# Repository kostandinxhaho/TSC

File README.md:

# OpenBook eReader

This project is a minimalist eBook Reader called **OpenBook**, built around the ESP32-C6 platform. The device is contains:

  - **A 7.5-inch e-paper display**

  - **A Li-Po battery**

  - **USB-C charging**

  - **Navigation buttons**

The design focuses on energy efficiency and ease of use, featuring a simple interface managed via GPIOs. The primary goal is to provide an optimal e-reading experience with low power consumption and a comfortable display.

## System Overview

| **Component** | **Details** |
|---------------|-------------|
| **MCU** | ESP32-C6 – supports Wi-Fi 6, BLE, Zigbee, and Thread |
| **Display** | 7.5-inch E-Paper (800 x 480 resolution, ~44g) |
| **Sensors** | BME688 – measures gas, humidity, temperature, and pressure |
| **Storage** | External NOR Flash 64MB (SPI) <br> SD Card (SPI) for extra storage |
| **Power Supply** | Battery: CELLEVIA BATTERIES LP584174 (3.7V, 1800mAh) <br> LDO Voltage Regulator for a steady 3.3V |
| **RTC** | Real-Time Clock for keeping time even when powered off |
| **Charging** | MCP73831T – charges via USB-C |
| **Extras** | Test Pads for debugging <br> Qwiic interface for easy module expansion |

## Block Diagram

## Bill of Materials:
| **Component** | **Purchase Link** | **Datasheet Link** |
|---------------|-------------------|---------------------|
| 112A-TAAR-R03 ATTEND | [Buy on Digi-Key](https://www.digikey.com/en/products/detail/attend-technology/112A-TAAR-R03/17633923) | [Datasheet](https://www.snapeda.com/parts/112A-TAAR-R03/Attend/datasheet/) |
| BDS229G-TR | [Buy on Digi-Key](https://www.digikey.com/en/products/detail/rohm-semiconductor/BDS229G-TR/3663792) | [Datasheet](https://fscdn.rohm.com/en/products/databook/datasheet/ic/power/voltage_detector/bds229g-e.pdf) |
| ESP32 WROVER BME680 Sensor | [Buy on Mouser](https://www.mouser.com/ProductDetail/Bosch-Sensortec/BME680) | [Datasheet](https://www.bosch-sensortec.com/media/boschsensortec/downloads/datasheets/bst-bme680-ds001.pdf) |
| LED CHG_LED | [Buy on Mouser](https://www.mouser.com/ProductDetail/Wurth-Elektronik/150060SS75000) | [Datasheet](https://www.we-online.com/components/products/datasheet/150060SS75000.pdf) |
| Condensator C0402 | [Buy on Digi-Key](https://www.digikey.com/en/products/detail/murata-electronics/GRM155R71C104KA88D/675947) | [Datasheet](https://search.murata.co.jp/Ceramy/image/img/A01X/G101/ENG/GRM155R71C104KA88-01.pdf) |
| Condensator Tant | [Buy on Digi-Key](https://www.digikey.com/en/products/detail/kemet/T491A106K016AT/2336183) | [Datasheet](https://search.kemet.com/download/datasheet/T491A106K016AT) |
| Q1 DMG2305UX-7 | [Buy on Mouser](https://www.mouser.com/ProductDetail/Diodes-Incorporated/DMG2305UX-7) | [Datasheet](https://www.diodes.com/assets/Datasheets/DMG2305UX.pdf) |
| RTC MODULE DS3231SN# | [Buy on Digi-Key](https://www.digikey.com/en/products/detail/analog-devices-inc-maxim-integrated/DS3231SN/1197576) | [Datasheet](https://www.analog.com/media/en/technical-documentation/data-sheets/DS3231.pdf) |
| ESP32 C6 WROOM-1-N8 | [Buy on Digi-Key](https://www.digikey.com/en/products/detail/espressif-systems/ESP32-C6-WROOM-1-N8/17728866) | [Datasheet](https://www.espressif.com/sites/default/files/documentation/esp32-c6-wroom-1_wroom-1u_datasheet_en.pdf) |
| FH34SRJ-24S-0.5SH(99) | [Buy on Digi-Key](https://www.digikey.com/en/products/detail/hirose-electric-co-ltd/FH34SRJ-24S-0-5SH-99/5132529) | [Datasheet](https://www.hirose.com/product/p/CL0580-1255-6-99) |
| MAX17048G+T10 | [Buy on Mouser](https://www.mouser.com/ProductDetail/Analog-Devices/MAX17048G+T10) | [Datasheet](https://www.analog.com/media/en/technical-documentation/data-sheets/max17048-max17049.pdf) |
| MBR0530 Schottky Diode | [Buy on Mouser](https://www.mouser.com/ProductDetail/onsemi/MBR0530T1G) | [Datasheet](https://www.onsemi.com/pdf/datasheet/mbr0530t1-d.pdf) |
| ESP32 WROVER MCP73831 Power Management | [Buy on Adafruit](https://www.adafruit.com/product/4410) | [Datasheet](https://ww1.microchip.com/downloads/en/DeviceDoc/20001984g.pdf) |
| PFMF.050.1 | [Buy on Mouser](https://www.mouser.com/ProductDetail/Littelfuse/PFMF050-1) | [Datasheet](https://www.littelfuse.com/~/media/electrical/datasheets/resettable-ptcs/littelfuse_ptc_pfmf_datasheet.pdf) |
| PGB1010603MR | [Buy on Mouser](https://www.mouser.com/ProductDetail/Littelfuse/PGB1010603MR) | [Datasheet](https://www.littelfuse.com/~/media/electrical/datasheets/esd_suppressors/littelfuse_esd_supressor_pulse_guard_pgb0603.pdf) |
| QWIIC_RIGHT_ANGLE CONNECTOR | [Buy on SparkFun](https://www.sparkfun.com/products/14427) | [Datasheet](https://www.jst-mfg.com/product/pdf/eng/eSR.pdf) |
| Rezistență R0402 | [Buy on Mouser](https://www.mouser.com/c/passive-components/resistors/?manu=Yageo%20Phycomp%7CYAGEO&resistance=10%20kOhms&package=%2Fcase%7C0402) | [Datasheet](https://www.yageo.com/upload/media/product/product_search/datasheet/cpr/yageo-rc_series_datasheet_2018.pdf) |
| SD0805S020S1R0 | [Buy on Digi-Key](https://www.digikey.com/en/products/detail/littelfuse-inc/SD0805S020S1R0/736561) | [Datasheet](https://www.littelfuse.com/~/media/electrical/datasheets/resettable-ptcs/littelfuse_ptc_sd0805_series.pdf) |
| Si1308EDL-T1-GE3 MOSFET | [Buy on Mouser](https://www.mouser.com/ProductDetail/Vishay/SI1308EDL-T1-GE3) | [Datasheet](https://www.vishay.com/docs/63442/si1308edl.pdf) |
| USB4110-GF-A | [Buy on Mouser](https://www.mouser.com/ProductDetail/GCT/USB4110-GF-A) | [Datasheet](https://gct.co/drawings/usb4110.pdf) |
| USBLC6-2SC6Y | [Buy on Mouser](https://www.mouser.com/ProductDetail/STMicroelectronics/USBLC6-2SC6Y) | [Datasheet](https://www.st.com/resource/en/datasheet/usblc6-2sc6.pdf) |
| W25Q512JVEIQ | [Buy on Mouser](https://www.mouser.com/ProductDetail/Winbond/W25Q512JVEIQ) | [Datasheet](https://www.winbond.com/resource-files/w25q512jv%20revg%2011022019%20plus.pdf) |
| XC6220A331MR-G | [Buy on Digi-Key](https://www.digikey.com/en/products/detail/torex-semiconductor-ltd/XC6220A331MR-G/5027707) | [Datasheet](https://www.torexsemi.com/file/xc6220/XC6220.pdf) |
| 744043680 BOBINA | [Buy on Mouser](https://www.mouser.com/ProductDetail/Wurth-Elektronik/744043680) | [Datasheet](https://katalog.we-online.com/pbs/datasheet/744043680.pdf) |

## Power Supply & Battery Management

The system supports dual power sources:

- **USB-C (5V) input**
- **3.7V Li-Po battery (CELLEVIA LP584174, 1800mAh)**

Power is managed as follows:

- **MCP73831** – Charges the Li-Po battery when USB-C is connected
- **LDO Voltage Regulator** – Converts 5V USB input to 3.3V

##  Sensors & Real-Time Clock (RTC)

Connected via the I²C bus:

- **BME688** – Measures temperature, humidity, pressure, and VOCs
- **DS3231** – High-precision RTC with battery backup

Sensor readings are processed locally and can be used for both display and logging.

## E-Paper Display

The **7.5-inch E-Ink display** interfaces over SPI and is controlled using:

- `EPD_CS` – Chip Select  
- `EPD_DC` – Data/Command  
- `EPD_RST` – Reset  
- `EPD_BUSY` – Busy indicator

The display only consumes energy when refreshing. Once the image is rendered, it holds static content without any power draw — perfect for long battery life.

## ESP32-C6 Connection

The following table shows the core hardware connections between the ESP32-C6 and its peripherals, organized by function:

| **Function**         | **ESP32-C6 Pins**                                                                 |
|----------------------|-----------------------------------------------------------------------------------|
| **Power & Reset**    | 3V3, GND, EN                                                                      |
| **USB-C**            | GPIO13 (USB_D+), GPIO14 (USB_D−)                                                  |
| **SD Card (SPI)**    | GPIO27 (MISO), GPIO7 (MOSI), GPIO6 (SCK), GPIO4 (SS_SD)                           |
| **E-Paper Display**  | GPIO11 (EPD_CS), GPIO5 (EPD_DC), GPIO21 (EPD_RST), GPIO26 (EPD_BUSY)              |
| **BME688 Sensor (I²C)** | GPIO19 (SDA), GPIO20 (SCL), GPIO17 (I2C_PWR)                                   |
| **UART**             | TXD0, RXD0                                                                        |
| **External Flash**   | FLASH_CS                                                                          |
| **Other Functions**  | IO/BOOT, RTC_PWM, RTC_RST, INT_RTC                                                |

## Communication Interfaces

- **SPI Bus**: Used by the E-Paper display, external Flash, and SD card. Each device has its own **chip select (CS)** pin to avoid conflicts.
- **I²C Bus**: Shared among BME688, RTC, and battery monitoring. Devices are addressable and use internal pull-ups for signal integrity.
- **UART**: Reserved for programming and serial monitoring via USB.
- **GPIOs**: Dedicated for user interaction (buttons, interrupts) or reserved for future extension.

## The project realization process

- Firstly I built the schematic using the model given in OCW, for the PCB model I followed the scheme respecting the given parameters.
- I created the ground planes with the GND signal on the top and bottom.
- Autorooted the paths, made the cables 0.3mm and 1.5mm respectively. Here I had to keep 1 of the cables the default size of 1.27 because it would create a lot of errors. (AIRCABLE)
- Made the battery and screen 3d models respecting the given parameters. Rendernd all the 3d models and the whole of them combined.

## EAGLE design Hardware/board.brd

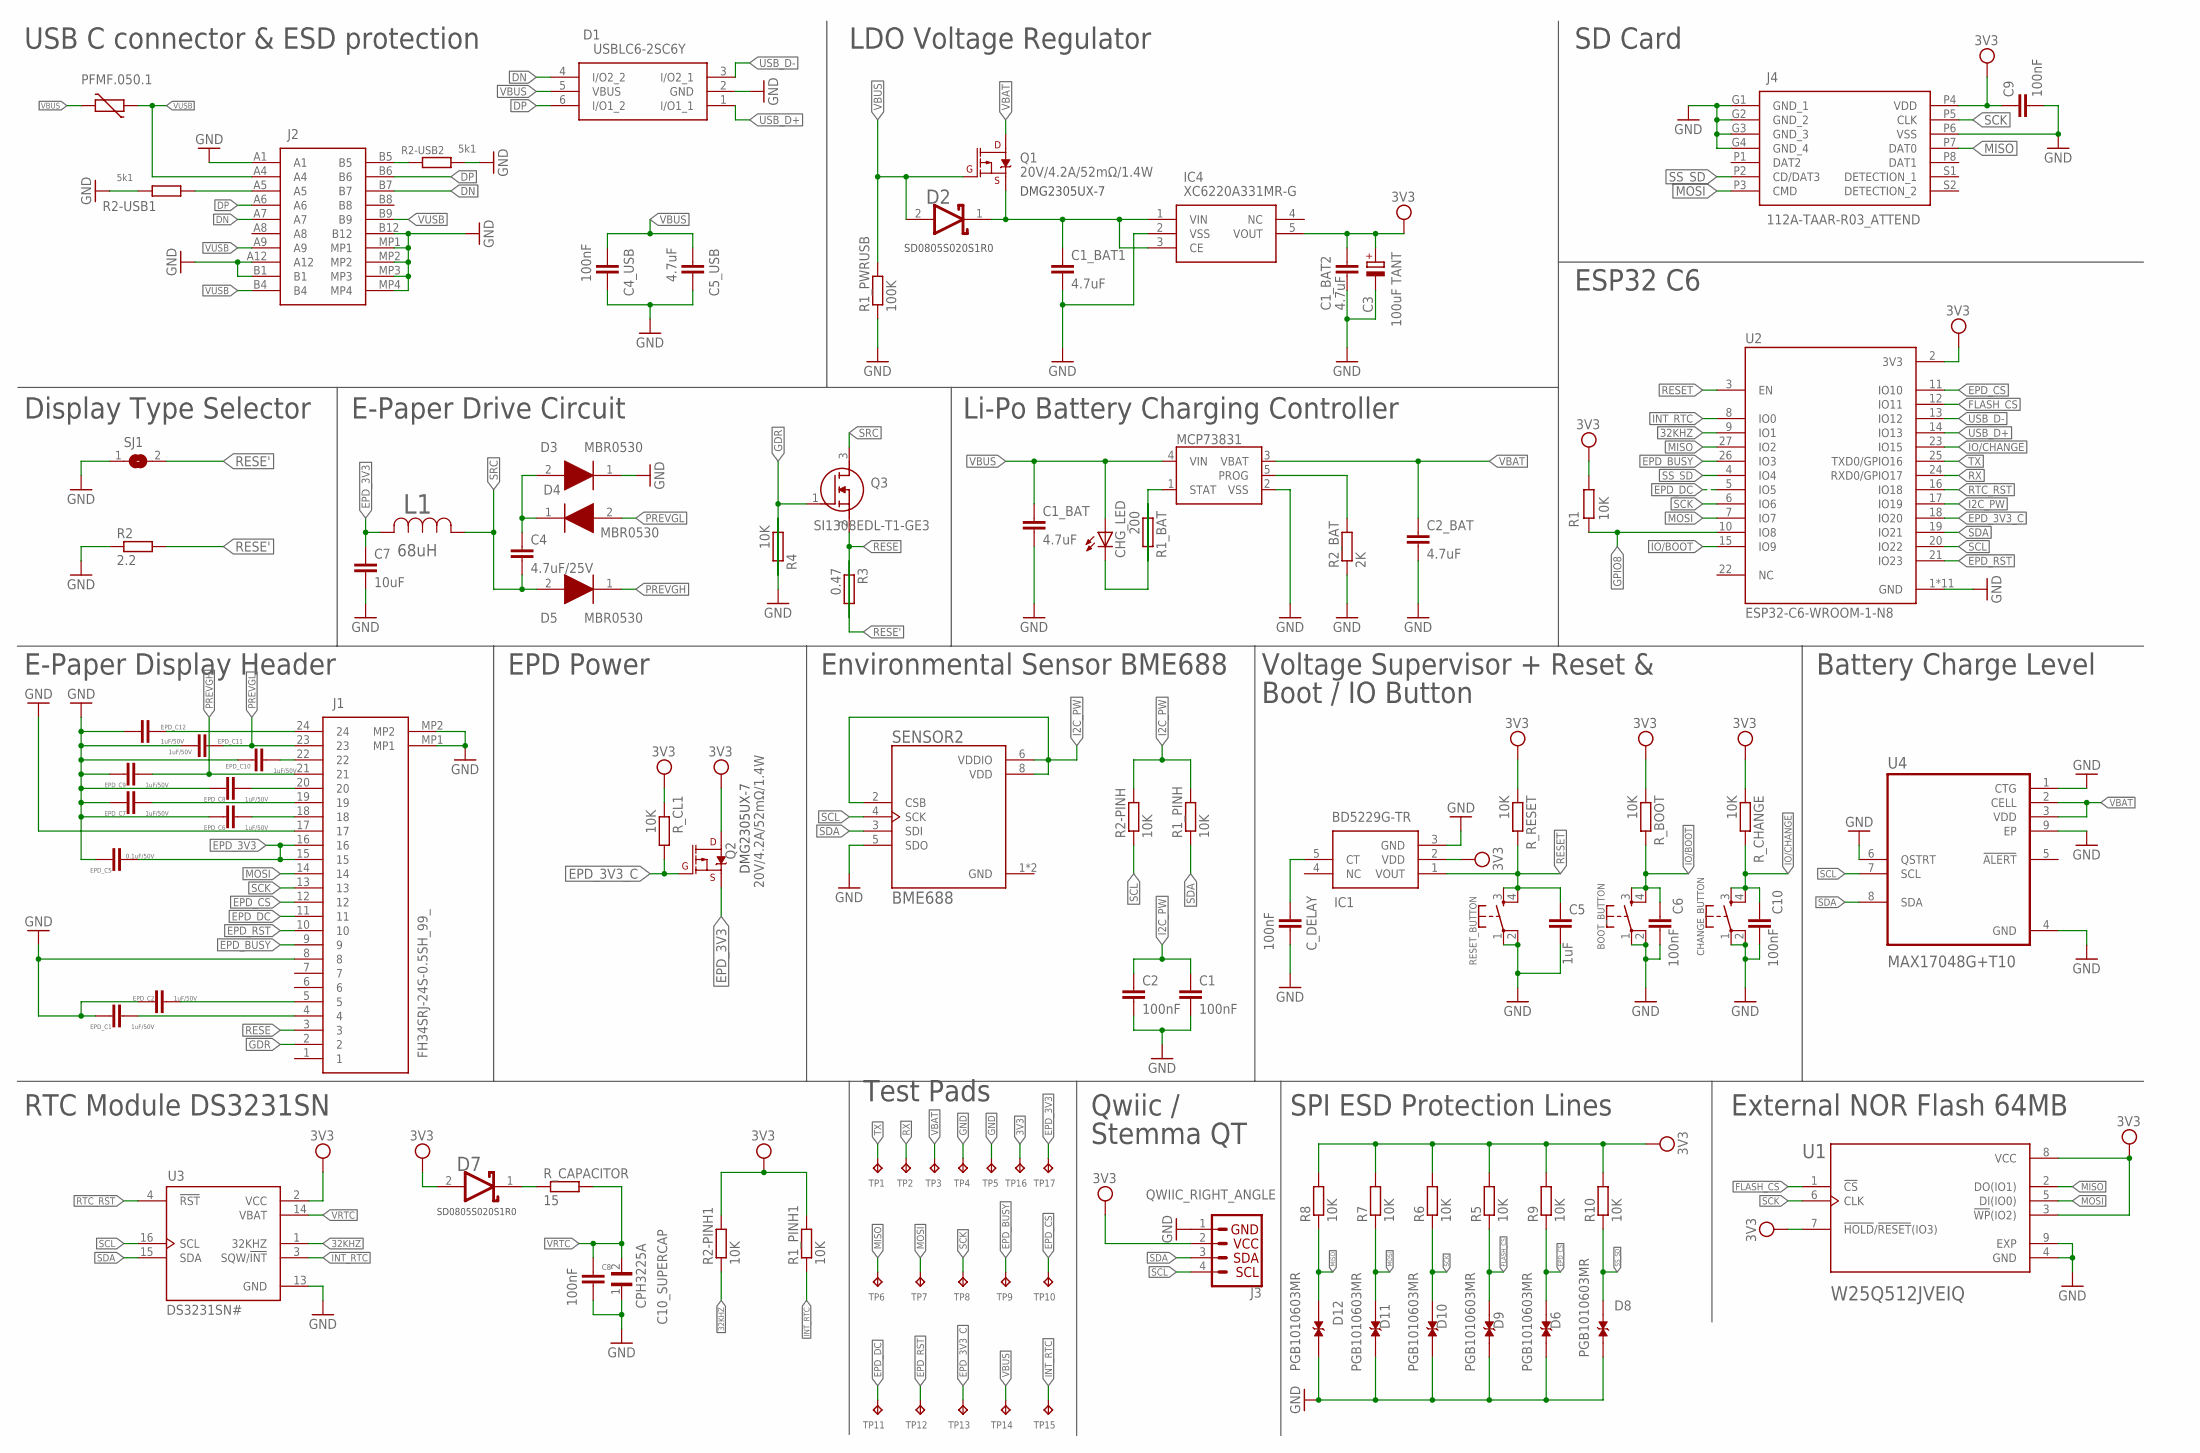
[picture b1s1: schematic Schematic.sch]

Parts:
BOOT_BUTTON: BUTTON_CUSYOMV1; MYBUTTON
C1, C2, C6, C8, C9, C10: 100nF; ESP32_WROVER_EAGLE-LTSPICE_C0402
C1_BAT, C1_BAT1, C1_BAT2, C2_BAT: 4.7uF; ESP32_WROVER_EAGLE-LTSPICE_C0402
C3: 100uF TANT; RCL_CT3528
C4: 4.7uF/25V; EAGLE-LTSPICE_C0402
C4_USB: 100nF; EAGLE-LTSPICE_C0402
C5: 1uF; ESP32_WROVER_EAGLE-LTSPICE_C0402
C5_USB: 4.7uF; EAGLE-LTSPICE_C0402
C7: 10uF; ESP32_WROVER_EAGLE-LTSPICE_C0402
C10_SUPERCAP: CPH3225A; CAPCP3225X100N
CHANGE_BUTTON: BUTTON_CUSYOMV1; MYBUTTON
CHG_LED: ADAFRUIT_LEDCHIP-LED0603; ADAFRUIT_CHIP-LED0603
C_DELAY: 100nF; ESP32_WROVER_EAGLE-LTSPICE_C0402
D1: USBLC6-2SC6Y; SOT95P280X145-6N
D2, D7: ESP32_WROVER_AVX---SD0805S020S1R0_AVX_SD0805S020S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; ESP32_WROVER_AVX---SD0805S020S1R0_AVX_SD0805S020S1R0_0
D3, D4, D5: MBR0530; SOD3716X135N
D6, D8, D9, D10, D11, D12: PGB1010603MR; DIOC1608X36N
EPD_C1, EPD_C2, EPD_C6, EPD_C7, EPD_C8, EPD_C9, EPD_C10, EPD_C11, EPD_C12: 1uF/50V; ESP32_WROVER_EAGLE-LTSPICE_C0402
EPD_C5: 0.1uF/50V; ESP32_WROVER_EAGLE-LTSPICE_C0402
IC1: BD5229G-TR; SOT95P280X125-5N
IC4: XC6220A331MR-G; SOT95P280X120-5N
J1: FH34SRJ-24S-0.5SH_99_; FH34SRJ24S05SH99
J2: SAMACSYS_PARTS_USB4110-GF-A; SAMACSYS_PARTS_USB4110GFA
J3: QWIIC_RIGHT_ANGLE; JST04_1MM_RA
J4: 112A-TAAR-R03_ATTEND; 112ATAARR03ATTEND
L1: 68uH; IND_4828-WE-TPC_WRE
MCP73831: ESP32_WROVER_SPARKFUN-IC-POWER_MCP73831; ESP32_WROVER_SPARKFUN-IC-POWER_SOT23-5
PFMF.050.1: ESP32C6_VARISTORCN1812; ESP32C6_VARISTOR_CT/CN1812
Q1, Q2: 20V/4.2A/52mΩ/1.4W; ESP32_WROVER_SPARKFUN-DISCRETESEMI_SOT23-3
Q3: SI1308EDL-T1-GE3; SOT65P210X110-3N
R1, R1_PINH, R1_PINH1, R2-PINH, R2-PINH1, R4, R5, R6, R7, R8, R9, R10: 10K; ESP32_WROVER_EAGLE-LTSPICE_R0402
R1_BAT: 200; ESP32_WROVER_EAGLE-LTSPICE_R0402
R1_PWRUSB: 100K; ESP32_WROVER_EAGLE-LTSPICE_R0402
R2: 2.2; ESP32_WROVER_EAGLE-LTSPICE_R0402
R2-USB1, R2-USB2: 5k1; ESP32_WROVER_EAGLE-LTSPICE_R0402
R2_BAT: 2K; ESP32_WROVER_EAGLE-LTSPICE_R0402
R3: 0.47; ESP32_WROVER_EAGLE-LTSPICE_R0402
RESET_BUTTON: BUTTON_CUSYOMV1; MYBUTTON
R_BOOT: 10K; ESP32_WROVER_EAGLE-LTSPICE_R0402
R_CAPACITOR: 15; ESP32_WROVER_EAGLE-LTSPICE_R0402
R_CHANGE: 10K; ESP32_WROVER_EAGLE-LTSPICE_R0402
R_CL1: 10K; ESP32_WROVER_EAGLE-LTSPICE_R0402
R_RESET: 10K; ESP32_WROVER_EAGLE-LTSPICE_R0402
SENSOR2: BME688; ESP32_WROVER_BME680_PSON80P300X300X100-8N
SJ1: SJ
TP1, TP2, TP3, TP4, TP5, TP6, TP7, TP8, TP9, TP10, TP11, TP12, TP13, TP14, TP15, TP16, TP17: TPTP20R; TP20R
U1: W25Q512JVEIQ; SON127P600X800X80-9N
U2: ESP32-C6-WROOM-1-N8; XCVR_ESP32-C6-WROOM-1-N8
U3: DS3231SN#; SOIC127P1032X265-16N
U4: MAX17048G+T10; SON50P200X200X80-9N

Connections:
3V3: C1_BAT2.1, C3.+, C9.1, D7.2 (ANODE), IC1.2 (VDD), IC4.5 (VOUT), J3.2, J4.P4 (VDD), Q2.3 (D), R1.1, R1_PINH1.2, R2-PINH1.2, R5.2, R6.2, R7.2, R8.2, R9.2, R10.2, R_BOOT.1, R_CHANGE.1, R_CL1.1, R_RESET.1, TP16.TP, U1.3 (!WP!(IO2)), U1.7 (!HOLD!/!RESET!(IO3)), U1.8 (VCC), U2.2 (3V3), U3.2 (VCC)
32KHZ: R2-PINH1.1, U2.9 (IO1), U3.1 (32KHZ)
DN: D1.4 (I/O2_2), J2.A7, J2.B7
DP: D1.6 (I/O1_2), J2.A6, J2.B6
EPD_3V3: C7.1, EPD_C5.1, J1.15, J1.16, L1.2, Q2.2 (S), TP17.TP
EPD_3V3_C: Q2.1 (G), R_CL1.2, TP13.TP, U2.18 (IO20)
EPD_BUSY: J1.9, TP9.TP, U2.26 (IO3)
EPD_CS: D6.2, J1.12, R9.1, TP10.TP, U2.11 (IO10)
EPD_DC: J1.11, TP11.TP, U2.5 (IO5)
EPD_RST: J1.10, TP12.TP, U2.21 (IO23)
FLASH_CS: D9.2, R5.1, U1.1 (!CS), U2.12 (IO11)
GDR: J1.2, Q3.1 (G), R4.2
GND: BOOT_BUTTON.1, BOOT_BUTTON.2, C1.2, C1_BAT.2, C1_BAT1.2, C1_BAT2.2, C2.2, C2_BAT.2, C3.-, C4_USB.2, C5.2, C5_USB.2, C6.2, C7.2, C8.2, C9.2, C10.2, C10_SUPERCAP.1, CHANGE_BUTTON.1, CHANGE_BUTTON.2, C_DELAY.2, D3.1 (K), D6.1, D8.1, D9.1, D10.1, D11.1, D12.2, EPD_C1.2, EPD_C2.2, IC1.3 (GND), IC4.2 (VSS), J1.8, J1.17, J1.MP1, J1.MP2, J2.A1, J2.A12, J2.B1, J2.B12, J2.MP1, J2.MP2, J2.MP3, J2.MP4, J3.1, J4.G1 (GND_1), J4.G2 (GND_2), J4.G3 (GND_3), J4.G4 (GND_4), J4.P6 (VSS), MCP73831.2 (VSS), R1_PWRUSB.1, R2.1, R2-USB1.1, R2-USB2.2, R2_BAT.1, R4.1, RESET_BUTTON.1, RESET_BUTTON.2, SENSOR2.1 (GND), SENSOR2.5 (SDO), SENSOR2.7 (GND), SJ1.1, TP4.TP, TP5.TP, U1.4 (GND), U1.9 (EXP), U2.1 (GND), U2.28 (GND), U2.29_1 (GND), U2.29_2 (GND), U2.29_3 (GND), U2.29_4 (GND), U2.29_5 (GND), U2.29_6 (GND), U2.29_7 (GND), U2.29_8 (GND), U2.29_9 (GND), U3.13 (GND), U4.1 (CTG), U4.4 (GND), U4.6 (QSTRT), U4.9 (EP)
GPIO8: R1.2, U2.10 (IO8)
I2C_PW: C1.1, C2.1, R1_PINH.2, R2-PINH.2, SENSOR2.2 (CSB), SENSOR2.6 (VDDIO), SENSOR2.8 (VDD), U2.17 (IO19)
INT_RTC: R1_PINH1.1, TP15.TP, U2.8 (IO0), U3.3 (SQW/!INT)
IO/BOOT: BOOT_BUTTON.3, BOOT_BUTTON.4, C6.1, R_BOOT.2, U2.15 (IO9)
IO/CHANGE: C10.1, CHANGE_BUTTON.3, CHANGE_BUTTON.4, R_CHANGE.2, U2.23 (IO15)
MISO: D12.1, J4.P7 (DAT0), R8.1, TP6.TP, U1.2 (DO(IO1)), U2.27 (IO2)
MOSI: D11.2, J1.14, J4.P3 (CMD), R7.1, TP7.TP, U1.5 (DI(IO0)), U2.7 (IO7)
unnamed: J2.A5, R2-USB1.2
unnamed: J2.B5, R2-USB2.1
unnamed: C1_BAT1.1, D2.1 (CATHODE), IC4.1 (VIN), IC4.3 (CE), Q1.2 (S)
unnamed: C4.1, D3.2 (A), D4.1 (K)
unnamed: MCP73831.5 (PROG), R2_BAT.2
unnamed: MCP73831.1 (STAT), R1_BAT.2
unnamed: CHG_LED.C, R1_BAT.1
unnamed: EPD_C12.1, J1.24
unnamed: C_DELAY.1, IC1.5 (CT)
unnamed: EPD_C10.1, J1.22
unnamed: EPD_C6.1, J1.18
unnamed: EPD_C5.2, EPD_C6.2, EPD_C7.2, EPD_C8.2, EPD_C9.2, EPD_C10.2, EPD_C11.2, EPD_C12.2
unnamed: EPD_C7.1, J1.19
unnamed: EPD_C8.1, J1.20
unnamed: D7.1 (CATHODE), R_CAPACITOR.1
unnamed: EPD_C2.1, J1.5
unnamed: EPD_C1.1, J1.4
PREVGH: D5.1 (K), EPD_C9.1, J1.21
PREVGL: D4.2 (A), EPD_C11.1, J1.23
RESE: J1.3, Q3.2 (S), R3.2
RESE': R2.2, R3.1, SJ1.2
RESET: C5.1, IC1.1 (VOUT), RESET_BUTTON.3, RESET_BUTTON.4, R_RESET.2, U2.3 (EN)
RTC_RST: U2.16 (IO18), U3.4 (!RST)
RX: TP2.TP, U2.24 (RXD0/GPIO17)
SCK: D10.2, J1.13, J4.P5 (CLK), R6.1, TP8.TP, U1.6 (CLK), U2.6 (IO6)
SCL: J3.4, R2-PINH.1, SENSOR2.4 (SCK), U2.20 (IO22), U3.16 (SCL), U4.7 (SCL)
SDA: J3.3, R1_PINH.1, SENSOR2.3 (SDI), U2.19 (IO21), U3.15 (SDA), U4.8 (SDA)
SRC: C4.2, D5.2 (A), L1.1, Q3.3 (D)
SS_SD: D8.2, J4.P2 (CD/DAT3), R10.1, U2.4 (IO4)
TX: TP1.TP, U2.25 (TXD0/GPIO16)
USB_D+: D1.1 (I/O1_1), U2.14 (IO13)
USB_D-: D1.3 (I/O2_1), U2.13 (IO12)
VBAT: C2_BAT.1, MCP73831.3 (VBAT), Q1.3 (D), TP3.TP, U4.2 (CELL), U4.3 (VDD)
VBUS: C1_BAT.1, C4_USB.1, C5_USB.1, CHG_LED.A, D1.5 (VBUS), D2.2 (ANODE), MCP73831.4 (VIN), PFMF.050.1.2, Q1.1 (G), R1_PWRUSB.2, TP14.TP
VRTC: C8.1, C10_SUPERCAP.2, R_CAPACITOR.2, U3.14 (VBAT)
VUSB: J2.A4, J2.A9, J2.B4, J2.B9, PFMF.050.1.1

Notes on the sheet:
SD0805S020S1R0
DMG2305UX-7
USB C connector & ESD protection
LDO Voltage Regulator
SD Card
Display Type Selector
E-Paper Drive Circuit
Li-Po Battery Charging Controller
ESP32 C6
E-Paper Display Header
EPD Power
Environmental Sensor BME688
Voltage Supervisor + Reset &
Boot / IO Button
Battery Charge Level
RTC Module DS3231SN
Test Pads
Qwiic /
Stemma QT
SPI ESD Protection Lines
External NOR Flash 64MB

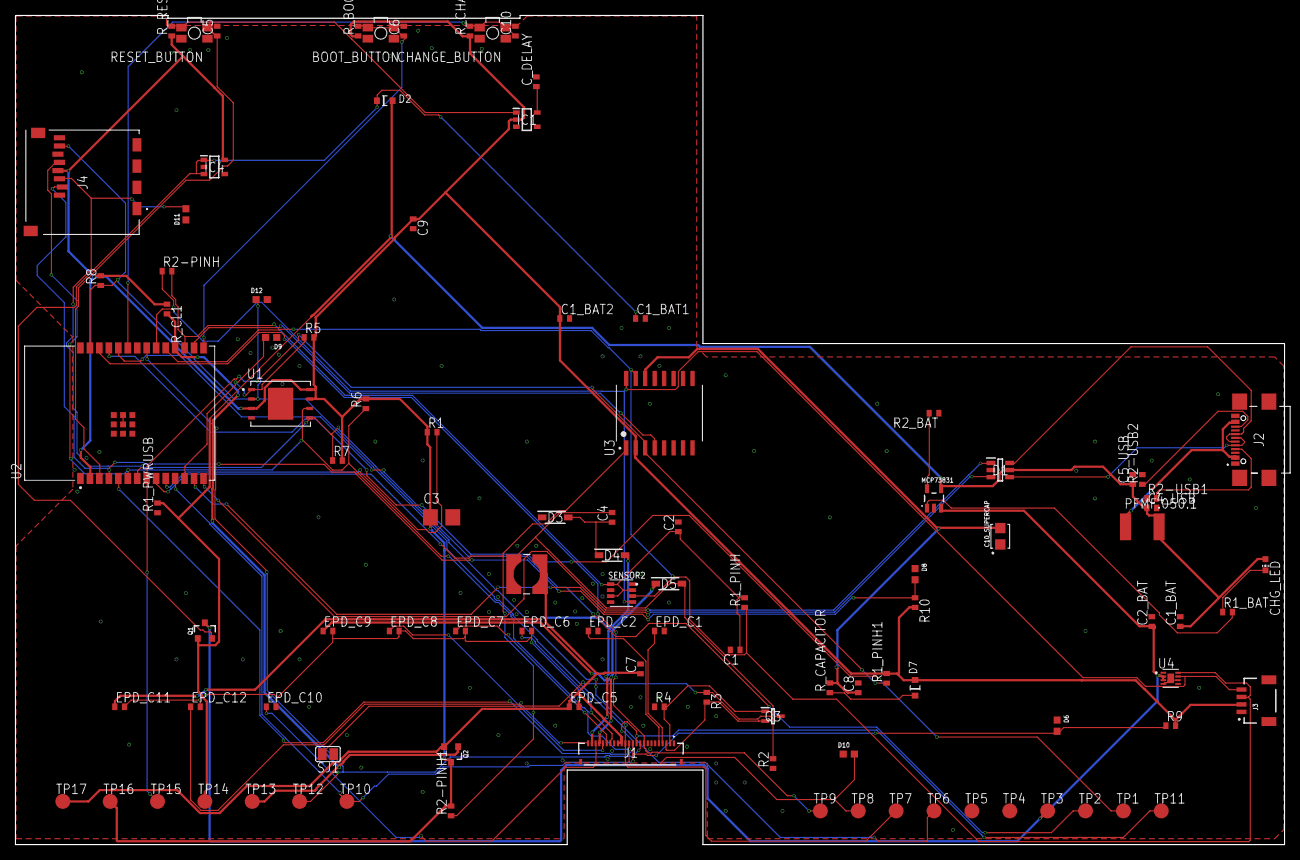
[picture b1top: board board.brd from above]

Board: 2 copper layers, 170.2 x 111.2 mm, 103 parts (0 on the bottom side), 56 nets.

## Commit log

2025-04-06 Firt commit
2025-04-06 Finished 70%
2025-04-06 Create LICENSE

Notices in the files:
parts and their libraries:
DeskAssistant v19 v1: COPYRIGHT: Copyright (C) 2024 Ultra Librarian. All rights reserved.
